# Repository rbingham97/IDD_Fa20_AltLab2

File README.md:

# IDD_Fa20_AltLab2

## Part A. Design your Arduino+

**a) What is the + improvement of your Arduino+**

For my Arduino+, I decided to add a second 2.5mm power jack to allow for a dedicated 12V power supply for LED components.

**b) What Arduino form-factor/design are you basing your design off of?**

The base board for this design is the Arduino UNO Rev3. 

**c) What features/parts need to be incorporated for your Arduino+? Include your research!**

I decided to use the PJ-102B 2.5mm barrel jack. This jack has a small form factor on the board itself, and handles up to 2.5A of current. The LED strip I plan to run from it pulls up to 2A of current, so the jack satisfies all design requirements. 

**d) What is the timeline for the overall development of your Arduino?**

After finishing this lab, I will submit the PCB order through OSH Park. I think OSH Park is the best option because they offer reasonably cheap prices while staying in range of domestic shipping. I've found that international shipping during the pandemic can be unreliable, so I'd rather avoid it. Shipping time is 15 days, after which I will solder the components to the board and attach all the peripheral systems. All told, system development should take under a month. 

**e) Which fabrication company are you using, what do you plan to order, and what is the design rationale for the selection?**

As stated above, I will be using OSH Park because I would like to avoid international shipping. My experience with international shipping during the pandemic was that it was slow and unreliable. 

## Part B. Order parts for your Arduino+
Develop a bill of materials for your Arduino +.

The BOM is [here](https://docs.google.com/spreadsheets/d/13ZLDKvZiJl-q5SsaYknf0bL7EgukQXHj2ZPbL3EwHSE/edit?usp=sharing).

## Part C. Prototype your Arduino+

**Describe key design questions (how big are the parts? what pins need to be connected?) and how you used/will use prototyping to answer them.**

The primary device that will interface with the board is a large string of LED lights that is integrated into my prototyping desk. To prototype, I will test the capability of a stock Arduino UNO to run the proper PWM signals from its digital pins, and I will rig up a 12V wall adapter directly to the power pin of the LED strip. I am still researching the proper way to interface with the LEDs and how to set up the power circuit, but I will complete a prototype before sending the board to be manufactured. 

## Part D. Layout your Arduino+

My EAGLE files are stored in this repository. I managed to fit the new part into the space between the digital pins and the Arduino logo on the original board, though doing this required me to sacrifice the board's UART interface. Since I don't anticipate using UART for anything, I cut the traces from digital pins 0 and 1, and instead grounded them to make room for the barrel jack's 3 large through hole solder points. 

## Part E. Send your board off to be made

Decided not to fab this version of the board, but am planning to fab a board for my project to get the learning. 

## Part F. Pain Points

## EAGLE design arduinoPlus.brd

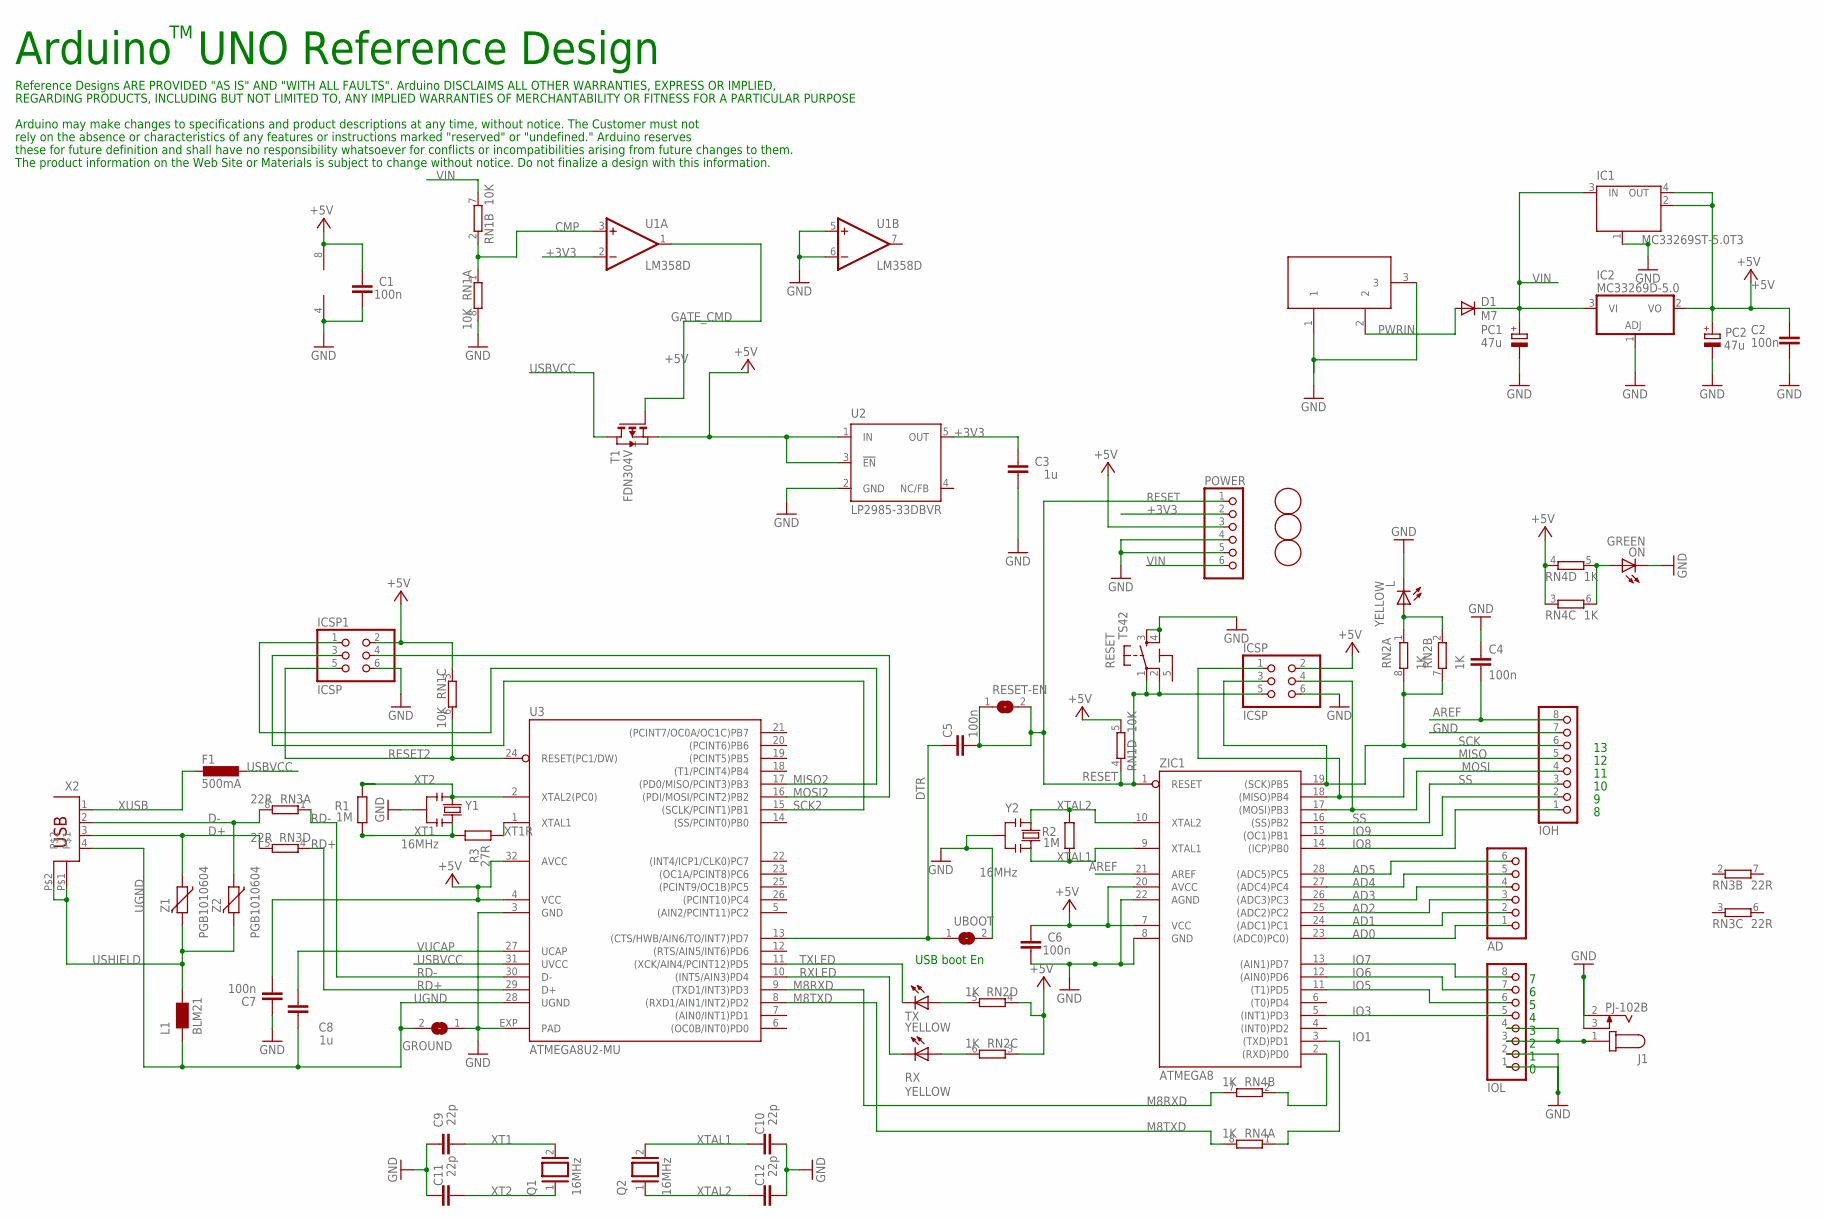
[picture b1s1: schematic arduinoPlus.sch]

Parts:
AD: PINHD-1X6; 1X06
C1, C2, C4, C5, C6, C7: 100n; C0603-ROUND
C3, C8: 1u; C0603-ROUND
C9, C10, C11, C12: 22p; C0603-ROUND
D1: M7; SMB
F1: 500mA; L1812
GROUND: SJ
IC1: MC33269ST-5.0T3; SOT223
IC2: MC33269D-5.0; DPACK
ICSP, ICSP1: ICSP; 2X03
IOH: PINHD-1X8; 1X08
IOL: PINHD-1X8; 1X08
J1: PJ-102B; CUI_PJ-102B
L: YELLOW; CHIP-LED0805
L1: BLM21; 0805
ON: GREEN; CHIP-LED0805
PC1, PC2: 47u; PANASONIC_D
POWER: PINHD-1X6; 1X06
Q1, Q2: 16MHz; QS
R1, R2: 1M; R0603-ROUND
R3: 27R; R0603-ROUND
RESET: TS42
RESET-EN: SJ
RN1: 10K; CAY16
RN2, RN4: 1K; CAY16
RN3: 22R; CAY16
RX: YELLOW; CHIP-LED0805
T1: FDN304V; SOT-23
TX: YELLOW; CHIP-LED0805
U1: LM358D; SO08
U2: LP2985-33DBVR; SOT23-DBV
U3: ATMEGA8U2-MU; QFN32
U$3, U$4, U$6: FIDUCIALMOUNT; FIDUCIA-MOUNT
UBOOT: SJ
X1: DC21MMX; DC-21MM
X2: PN61729
Y1, Y2: 16MHz; RESONATOR
Z1, Z2: PGB1010604; CT/CN0603
ZIC1: ATMEGA8; DIL28-3

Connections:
5-GND: RESET.5 (5-GND)
+3V3: C3.2, POWER.2, U1.2 (-IN), U2.5 (OUT)
+5V: C1.2, C2.2, C6.2, C7.1, IC1.2 (OUT), IC1.4 (OUT), IC2.2 (VO), ICSP.2, ICSP1.2, PC2.+, POWER.3, RN1.3 (1), RN1.5 (2), RN2.3 (1), RN2.4 (1), RN4.3 (1), RN4.4 (1), T1.2 (S), U1.8 (V+), U2.1 (IN), U2.3 (!EN), U3.4 (VCC), U3.32 (AVCC), ZIC1.7 (VCC), ZIC1.20 (AVCC)
+12V: IOL.3, IOL.4, J1.1
AD0: AD.1, ZIC1.23 ((ADC0)PC0))
AD1: AD.2, ZIC1.24 ((ADC1)PC1)
AD2: AD.3, ZIC1.25 ((ADC2)PC2)
AD3: AD.4, ZIC1.26 ((ADC3)PC3)
AD4: AD.5, ZIC1.27 ((ADC4)PC4)
AD5: AD.6, ZIC1.28 ((ADC5)PC5)
AREF: C4.2, IOH.8, ZIC1.21 (AREF)
CMP: RN1.1, RN1.2 (1), U1.3 (+IN)
D+: RN3.5 (2), X2.3, Z1.1
D-: RN3.8 (2), X2.2, Z2.1
DTR: C5.1, U3.13 ((CTS/HWB/AIN6/TO/INT7)PD7), UBOOT.1
GATE_CMD: T1.3 (G), U1.1 (OUT)
GND: C1.1, C2.1, C3.1, C4.1, C6.1, C7.2, C9.2, C10.1, C11.2, C12.1, GROUND.1, IC1.1 (GND/ADJ), IC2.1 (ADJ), ICSP.6, ICSP1.6, IOH.7, IOL.1, IOL.2, J1.2, J1.3, L.C, ON.C, PC1.-, PC2.-, POWER.4, POWER.5, RESET.3, RESET.4, RN1.8 (2), U1.4 (V-), U1.5 (+IN), U1.6 (-IN), U2.2 (GND), U3.3 (GND), U3.EXP (PAD), UBOOT.2, X1.1, X1.3, Y1.2, Y2.2, ZIC1.8 (GND), ZIC1.22 (AGND)
IO0: RN4.2 (1), ZIC1.2 ((RXD)PD0)
IO1: RN4.1, ZIC1.3 ((TXD)PD1)
IO3: IOL.5, ZIC1.5 ((INT1)PD3)
IO5: IOL.6, ZIC1.11 ((T1)PD5)
IO6: IOL.7, ZIC1.12 ((AIN0)PD6)
IO7: IOL.8, ZIC1.13 ((AIN1)PD7)
IO8: IOH.1, ZIC1.14 ((ICP)PB0)
IO9: IOH.2, ZIC1.15 ((OC1)PB1)
M8RXD: RN4.7 (2), U3.9 ((TXD1/INT3)PD3)
M8TXD: RN4.8 (2), U3.8 ((RXD1/AIN1/INT2)PD2)
MISO: ICSP.1, IOH.5, ZIC1.18 ((MISO)PB4)
MISO2: ICSP1.1, U3.17 ((PD0/MISO/PCINT3)PB3)
MOSI: ICSP.4, IOH.4, ZIC1.17 ((MOSI)PB3)
MOSI2: ICSP1.4, U3.16 ((PDI/MOSI/PCINT2)PB2)
unnamed: L.A, RN2.1, RN2.2 (1)
unnamed: ON.A, RN4.5 (2), RN4.6 (2)
unnamed: RN2.6 (2), RX.A
unnamed: RN2.5 (2), TX.A
PWRIN: D1.A, X1.2
RD+: RN3.4 (1), U3.29 (D+)
RD-: RN3.1, U3.30 (D-)
RESET: C5.2, ICSP.5, POWER.1, RESET.1, RESET.2, RESET-EN.1, RESET-EN.2, RN1.4 (1), ZIC1.1 (RESET)
RESET2: ICSP1.5, RN1.6 (2), U3.24 (RESET(PC1/DW))
RXLED: RX.C, U3.10 ((INT5/AIN3)PD4)
SCK: ICSP.3, IOH.6, RN2.7 (2), RN2.8 (2), ZIC1.19 ((SCK)PB5)
SCK2: ICSP1.3, U3.15 ((SCLK/PCINT1)PB1)
SS: IOH.3, ZIC1.16 ((SS)PB2)
TXLED: TX.C, U3.11 ((XCK/AIN4/PCINT12)PD5)
UGND: C8.2, GROUND.2, L1.1, U3.28 (UGND), X2.4
USBVCC: F1.1, T1.1 (D), U3.31 (UVCC)
USHIELD: L1.2, X2.P$1, X2.P$2, Z1.2, Z2.2
VIN: D1.C, IC1.3 (IN), IC2.3 (VI), PC1.+, POWER.6, RN1.7 (2)
VUCAP: C8.1, U3.27 (UCAP)
XT1: C9.1, Q1.2, R1.1, R3.2, Y1.3
XT1R: R3.1, U3.1 (XTAL1)
XT2: C11.1, Q1.1, R1.2, U3.2 (XTAL2(PC0)), Y1.1
XTAL1: C10.2, Q2.2, R2.1, Y2.3, ZIC1.9 (XTAL1)
XTAL2: C12.2, Q2.1, R2.2, Y2.1, ZIC1.10 (XTAL2)
XUSB: F1.2, X2.1

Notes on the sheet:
Arduino UNO Reference Design
USB boot En
Reference Designs ARE PROVIDED "AS IS" AND "WITH ALL FAULTS". Arduino DISCLAIMS ALL OTHER WARRANTIES, EXPRESS OR IMPLIED,
Arduino may make changes to specifications and product descriptions at any time, without notice. The Customer must not
REGARDING PRODUCTS, INCLUDING BUT NOT LIMITED TO, ANY IMPLIED WARRANTIES OF MERCHANTABILITY OR FITNESS FOR A PARTICULAR PURPOSE
rely on the absence or characteristics of any features or instructions marked "reserved" or "undefined." Arduino reserves
these for future definition and shall have no responsibility whatsoever for conflicts or incompatibilities arising from future changes to them.
The product information on the Web Site or Materials is subject to change without notice. Do not finalize a design with this information.

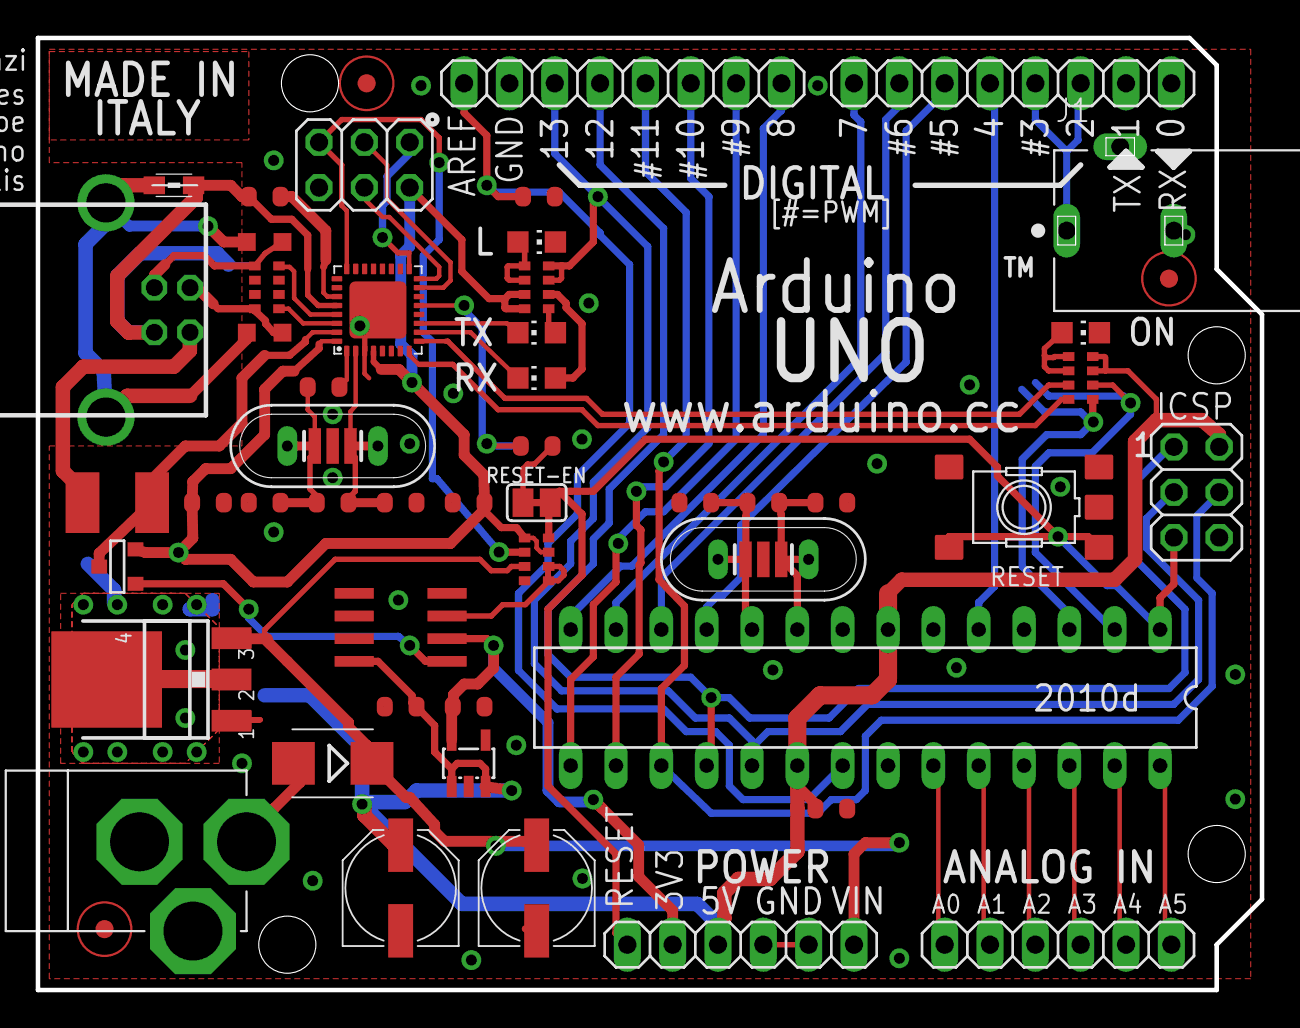
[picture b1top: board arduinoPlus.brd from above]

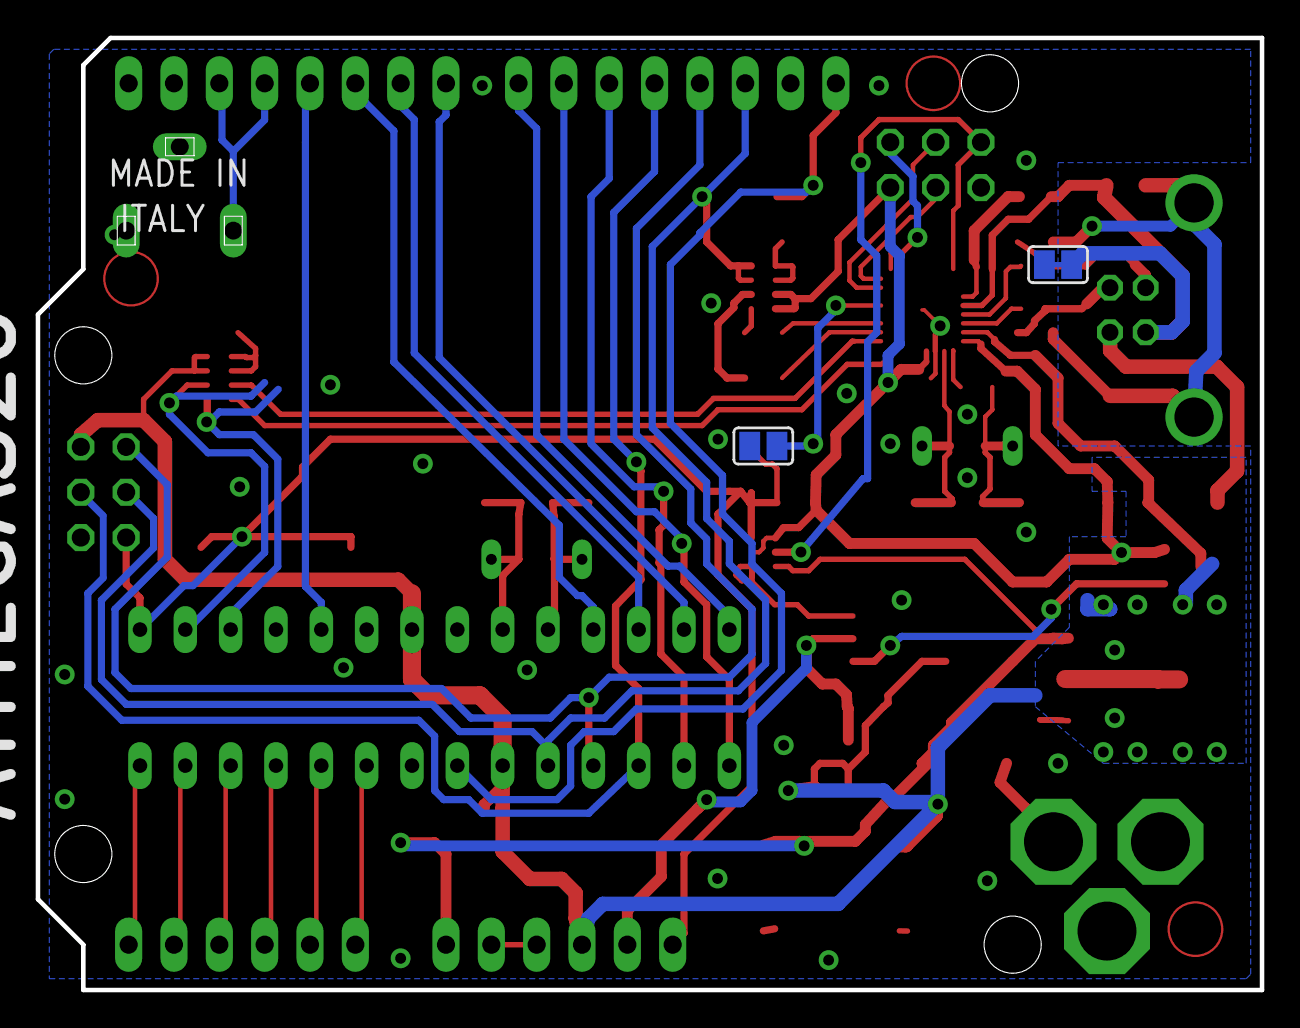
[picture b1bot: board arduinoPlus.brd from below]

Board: 2 copper layers, 68.6 x 53.3 mm, 57 parts (2 on the bottom side), 55 nets.

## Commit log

2020-09-11 prelab
2020-09-16 Question Answers 9/15/20
2020-09-16 EAGLE Files
2020-09-24 BOM Link
